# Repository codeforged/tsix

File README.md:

# TSIX

**TSIX** is an **operating system simulator** built entirely in TypeScript on top of Node.js/V8 — complete with a custom kernel, syscall dispatcher, logical Unix-style permission layer (UID/GID, rwx), POSIX-like filesystem, signal handling, and device abstraction (HAL). It is **not a VM that emulates a CPU**; it simulates OS concepts — tasks/processes, permissions, filesystems, signals — directly within the Node.js runtime as an educational and experimental project, and follows **Unix fidelity** as its design north star (see [Philosophy](#philosophy)).

Its flagship use case is a complete **IoT stack** — the MQTNL protocol (MQTT-based), OTA firmware updates, real-time dashboards, and encrypted remote terminal access — all reachable with nothing more than an internet connection and a free MQTT broker. No VPS, no static public IP, no paid cloud service required.

**Where IoT fits (and where it doesn't):** the IoT stack is **not** part of the kernel. TSIX's core — kernel, VFS, drivers (rings 1–2) — is generic within the simulator's ecosystem: it has no idea what MQTT, OTA, or ESP32 are. The IoT stack is simply **one application running on top of the platform**, exactly like the window manager, the file browser, or the shell. That separation *is* the design's strength: one neutral, Unix-faithful core powers any generic simulated task — be it IoT, a desktop environment, or a command line.

TSIX keeps evolving, so expect rough edges and breaking changes between versions.

<p align="center">
  
  <br>
  <em>Ring 1 — Kernel Core (Syscalls, Scheduler, Permission, Mount, GUI Registry).</em>
</p>

<p align="center">
  
  <br>
  <em>Ring 2 — HAL &amp; File System (BKFS, RamFS, HostVFS, device drivers).</em>
</p>

<p align="center">
  
  <br>
  <em>Ring 3 — User Libraries (UserLib, NetworkLib, Emerald, WorkerEntry).</em>
</p>

<p align="center">
  
  <br>
  <em>Ring 4 — Applications (init, shell, daemons, Asteracea WM, GUI apps).</em>
</p>

<p align="center">
  
  <br>
  <em>GUI / Display Pipeline (Emerald → kernel → DOME → browser).</em>
</p>

<p align="center">
  
  <br>
  <em>Networking &amp; IoT Stack (MQTNL → E2E → MQTT → OTA/SCP/TSSH/ESP32).</em>
</p>

<p align="center">
  
  <br>
  <em>TSIX console — TTY login &amp; shell.</em>
</p>

<p align="center">
  
  <br>
  <em>Asteracea Window Manager — desktop environment (taskbar, launcher, apps).</em>
</p>

### Why TSIX exists

This project started in 2021 as a way to remotely manage home automation — lights controlled/monitored by a Raspberry Pi, MCP23017, and relays — while living between two cities and only being home on weekends. Renting a VPS with a static public IP just to check on the lights wasn't worth it. What began as a small utility (originally called **NOS**) grew, over several years, into TSIX: a full operating-system-style platform with an IoT stack as its most complete, most battle-tested application.

---

## Key Features

### Kernel

| Feature                | Detail                                                                                                     |
| ---------------------- | ---------------------------------------------------------------------------------------------------------- |
| **Syscall Dispatcher** | 60+ POSIX-inspired syscalls (OPEN, READ, WRITE, EXEC, WAITPID, SIGNAL, CHMOD...)                           |
| **Scheduler**          | Process manager: PCB states, wait queue, signals (SIGKILL, SIGTERM, SIGINT, SIGSTOP...) — each process runs in its own Worker Thread |
| **Permission Manager** | UID/GID, rwx bits, root bypass, SetUID & Saved UID (suid) support                                          |
| **Mount Manager**      | Multi-VFS overlay, bind mount, union mount, nested mount points                                            |
| **Process Tree**       | Parent-child links, orphan auto-reparent to init, zombie prevention                                        |
| **IPC**                | Built-in `SEND_MSG` syscall + UUID-based identity messaging                                                |

### Filesystem (VFS)

| Feature               | Detail                                                                          |
| --------------------- | ------------------------------------------------------------------------------- |
| **BKFS (SQLite VFS)** | Persistent filesystem in a single `.db` file, path traversal via parent_id tree |
| **RAM VFS**           | In-memory tree for the root filesystem (tmpfs-like)                             |
| **HostVFS**           | Bridge to the host filesystem (`/mnt/host`) via Node.js `fs`                    |
| **Chunked I/O**       | `readChunk`/`writeChunk` for progress-aware file operations                     |
| **Unix Permissions**  | Owner/group/others, mode rwx, SetUID bit                                        |

### Networking

| Feature            | Detail                                                                   |
| ------------------ | ------------------------------------------------------------------------ |
| **MQTNL Protocol** | Binary + JSON encoding, CRC32 validation, magic bytes, version handshake |
| **E2E Encryption** | RSA-2048 handshake + ChaCha20-Poly1305 session encryption                |
| **OTA Updates**    | Over-the-air firmware update via MQTNL protocol                          |
| **SCP**            | Secure file transfer with encryption + password authentication           |
| **TSSH**           | Encrypted remote terminal to a TSIX node from anywhere — internet + MQTT broker only, **no public IP / VPS required**. SSH-like RSA-2048 handshake → ChaCha20-Poly1305 session (successor of AirTerm) |

### Remote Terminal — TSSH (no VPS, no public IP)

**TSSH** is TSIX's encrypted remote terminal (secure shell). Unlike classic SSH, it
**does not need a VPS, a static public IP, or port-forwarding** — it rides on top of
the MQTT broker, which TSIX already speaks natively. The broker can be **local
(LAN)** or **public (internet)** — as long as both sides can reach it, they can
connect.

```
┌─────────────┐        MQTT broker         ┌─────────────┐
│  tssh (client) │  ───── local / internet ───▶  │  tsshd (daemon)  │
│  any TSIX node │                            │  target TSIX node │
└─────────────┘                            └─────────────┘
      │                                          │
      └──  no public IP · no VPS · no NAT hole ◀──┘
```

**Handshake** (SSH-like): the client asks the server's public key, then wraps a
fresh **ChaCha20-Poly1305** session key in **RSA-2048** and sends it back — after
which all terminal I/O is end-to-end encrypted over the MQTT broker.

```mermaid
sequenceDiagram
    autonumber
    participant C as tssh (client)
    participant B as MQTT broker (local/internet)
    participant S as tsshd (daemon)

    C->>B: HANDSHAKE_REQ
    B->>S: HANDSHAKE_REQ
    S-->>B: HANDSHAKE_RESP (RSA-2048 pubkey + fingerprint)
    B-->>C: HANDSHAKE_RESP

    Note over C,S: Verify host fingerprint (known_hosts)

    C->>B: KEY_EXCHANGE (session key, RSA-encrypted)
    B->>S: KEY_EXCHANGE
    S-->>B: CONNECT_ACK
    B-->>C: CONNECT_ACK

    Note over C,S: Session now ChaCha20-Poly1305 encrypted

    C->>B: CONNECT_REQ (encrypted: TTY / -c command)
    B->>S: CONNECT_REQ
    S-->>B: DATA / RESIZE / PING / EXIT (encrypted)
    B-->>C: DATA / RESIZE / PING / EXIT (encrypted)
    C->>B: DATA (keystrokes, encrypted)
    B->>S: DATA
```

**Try it** (two TSIX nodes on the same broker):

```bash
# on the target node
tsshd                # default: listens on MQTNL port 24

# from any other node (or the same one, via localhost)
tssh <hostname>      # e.g. tssh wintsix

tssh <hostname> -c "cat /etc/hostname"   # run a one-off remote command
```

> **Why this matters:** you can administer a TSIX node — or an ESP32 IoT device
> behind NAT — from anywhere, using only a free public MQTT broker. No VPS to
> rent, no firewall hole to open.

### GUI (Emerald + DOME)

| Feature             | Detail                                                                   |
| ------------------- | ------------------------------------------------------------------------ |
| **DOME Engine**     | WebSocket-based display server — renders UI in the browser               |
| **Emerald Widgets** | Screen, Window, button, div, input, lineChart, radialGauge, toggleSwitch |
| **Modal Dialogs**   | alert(), confirm(), question() — built-in                                |
| **Window Manager**  | Asteracea WM with taskbar, Z-index, focus management                     |

### Security

- **Process Isolation** — Each application runs in a separate Worker Thread
- **Sandbox** — Node.js host APIs are restricted in User-Land
- **Permission Model** — Unix rwx for files & devices
- **Root Privileges** — UID 0 bypasses all checks
- **Saved UID** — the login manager (WM) can re-elevate to root to switch users (restore `setuid(0)` via `pcb.suid`)
- **PID 1 Protection** — init cannot be killed directly

---

## Quick Start

### Prerequisites

- Node.js 18+
- npm

### Fresh Install

A fresh TSIX image is built with the `install` script. It creates a brand new database (`.db`) from the bundled root filesystem (`src/mirror` + `src/common`), asks for a few configuration values interactively, and writes them into `src/sysconfig.conf` (key-value, gaya `/etc/fstab.conf`).

```bash
git clone https://github.com/yourusername/tsix.git
cd tsix
npm install
npm run install
```

The installer will ask you for:

- Hostname (interface addresses are derived from it: `<hostname>`, `<hostname>_2`)
- Default login user
- MQTT broker address
- Default MQTT port
- Kernel verbose mode (y/n)
- New database path
- (Optional) root password

> [!NOTE] **Default credentials**
>
> - **User:** `root` — **Password:** `root` (default; bcrypt hash bundled in `src/mirror/etc/shadow`).
> - Change the password by answering the **root-password prompt** during `npm run install`, or run `passwd` inside TSIX.
> - This is a **documented development default**, not a secret. For production or public exposure, always set your own password (don't use the default).

After installation, `src/sysconfig.conf` points to the new database and the system is ready to boot:

```bash
npm start
```

### Install Options

```bash
npm run install                              # interactive, db path from sysconfig
npm run install -- --path data/tsix.db       # install to a specific database file
npm run install -- --path data/tsix.db --force   # overwrite an existing db (auto-backup)
npm run install -- --defaults                # non-interactive, use all defaults
npm run install -- --no-config               # skip writing src/sysconfig.conf
```

### Safe Mode

If the system fails to boot (e.g. a bad daemon in `rc.local`), start it with
the startup scripts disabled:

```bash
npm start -- --safe-mode
```

Safe mode skips `/etc/rc.local` (startup daemons) so you can log in and fix
the problem.

### Utility Scripts

```bash
npm run vfs:bootstrap        # bulk-sync src/mirror into the configured database
npm run bkfs:create          # create an empty database (path from sysconfig)
node scripts/clean_bloat.js  # truncate syslog + vacuum the database
```

All scripts resolve the default database path from `kernel.database` in `src/sysconfig.conf` (shared via `scripts/lib/db-path.ts`), so they stay in sync with the path chosen at install time.

### GUI Mode

```bash
# Terminal 1 — Start DOME Engine
dome

# Open browser -> http://localhost:8080

# Terminal 2 (via TSIX shell) — Launch apps
asteracea           # Window Manager
file-cruiser        # File Manager GUI
eucalyptus          # Text Editor
```

---

## Architecture

```
Ring 0  -> Host OS / V8 Engine (reserved)
Ring 1  -> Kernel Core (Syscalls, Scheduler, Permission Manager)
Ring 2  -> Drivers & File System (HAL, BKFS, Device Drivers)
Ring 3  -> User Libraries (UserLib, FsLib, NetLib, StdLib)
Ring 4  -> Applications (/bin — shell, file-cruiser, tools)
```

> **IoT is not part of the kernel.** The IoT stack runs as a regular
> application in **Ring 4**, on top of the generic rings 1–3 — the kernel has
> no concept of MQTT, OTA, or ESP32. That neutrality is the point: one core
> runs IoT, a desktop environment, and a shell side by side.

### Data Flow

```
Application (Worker Thread)
    | postMessage (IPC)
    v
Syscall Dispatcher (Main Thread)
    | routing
    v
BKFS / Device Drivers / Scheduler
    | return
    v
Syscall Dispatcher
    | postMessage (IPC)
    v
Application
```

### Boot Sequence

```
bootstrap.sh -> main.ts -> Kernel.boot()
  -> Mount BKFS (SQLite VFS) root filesystem
  -> Process /etc/fstab.conf (mount /tmp as ramfs, etc.)
  -> Init TTYs (virtual consoles)
  -> Register Devices (keyboard, TTY, null, network)
  -> Init Serial Auto-Detection
  -> Load Device Configs + HAL drivers
  -> Pre-compile framework libraries into memory cache
  -> Ensure default auth & groups (/etc/passwd, /etc/shadow, users, sudo)
  -> Spawn PID 1 (/bin/init)
  -> init spawns login on TTYs + system daemons
  -> System Ready
```

---

## Project Structure

```
tsix/
├── src/
│   ├── common/        — Shared types (SyscallCode, GUITypes, IPCTypes)
│   ├── kernel/        — Kernel Core (Ring 1)
│   │   ├── Syscalls.ts        — 60+ syscall dispatcher
│   │   ├── Scheduler.ts       — Process manager (create, kill, waitpid)
│   │   ├── PermissionManager.ts — Unix rwx permission check
│   │   ├── MountManager.ts    — Multi-VFS overlay
│   │   ├── PortManager.ts     — TCP/UDP port allocation
│   │   ├── GUIRegistry.ts     — Window -> PID mapping
│   │   └── devices/           — Hardware drivers (TTY, Keyboard, Pipe, Socket...)
│   ├── vfs/           — Filesystem backends (BKFS, RamFS, HostVFS)
│   ├── mirror/        — Userland (Ring 4) — FHS layout (synced to VFS root)
│   │   ├── bin/       — 80+ command-line tools (ls, cat, tsh, sudo...)
│   │   ├── sbin/      — Daemons (tpkgd, scpd, tsshd, crond...)
│   │   ├── usr/       — User binaries (local/bin)
│   │   ├── opt/       — GUI apps (asteracea WM, dome, eucalyptus, file-cruiser...)
│   │   ├── lib/       — Libraries (Emerald, UserLib, Application)
│   │   ├── etc/       — Config (passwd, shadow, group, profile, fstab)
│   │   └── home/, root/, mnt/, var/ — User homes, mounts, logs
│   └── userland/      — Worker entry point
├── wiki/              — Full documentation
├── scripts/           — Build, install & utility scripts
└── platformio/        — ESP32 firmware examples
```

---

## Status

> Note: TSIX is an educational/experimental project. "Working" only means the component passes its test suite and boots in the reference environment — it is **not** production-ready. APIs and behavior may change without notice.

| Component                                                | Status      | Tests       |
| -------------------------------------------------------- | ----------- | ----------- |
| Kernel (syscalls, scheduler, perms, mount, devices, TTY) | Working     | 354/359     |
| VFS (BKFS, HostVFS)                                      | Working     | 150/150     |
| Common Utilities & Protocols (MQTNL)                     | Working     | 140/143     |
| GUI library (Emerald)                                    | Working     | 1/1         |
| **TOTAL**                                                | **Working** | **645/653** |

> [!NOTE] **7 test failures are pre-existing / environment-related** — 5 in `Syscalls` (e.g. `SCREEN_INFO` requires device setup), 2 in `Logger` (timestamp format). Two test files (`SecurityAgent`, `F1-UtilityScripts`) fail to load. Not related to feature changes.

---

## Use Cases

| Area              | Capability                                                         |
| :---------------- | :----------------------------------------------------------------- |
| **IoT Gateway**   | MQTNL protocol, OTA updates, ESP32 integration, Serial devices     |
| **Cloud Desktop** | DOME display server, Asteracea WM, PixelTerm, File Cruiser         |
| **Edge Platform** | TPKG package manager, crond scheduler, process isolation           |
| **Secure Tunnel** | TSSH (remote terminal), SCP (file transfer) with E2E encryption |
| **Dashboard**     | IoT dashboard with real-time charts via DOME                       |
| **Sandbox**       | Isolated script execution in Worker Threads                        |

---

## Philosophy

TSIX is inspired by the **UNIX philosophy**:

1. **Everything is a File** — Keyboard, display, socket, pipe, I2C device — everything is a file
2. **Distributed by Design** — Built-in IPC via SEND_MSG + identity-based messaging
3. **Small, Sharp Tools** — 80+ utilities that combine via pipes & redirection
4. **Security via Simplicity** — UID/GID permission model, process isolation, root privileges
5. **Unix Fidelity** — Emulating Unix/Linux behavior as closely as possible (semantics over mechanism); deviations are permitted only when constrained by the V8 runtime, and must be explicitly documented (see [Five Core Principles](wiki/course/01-philosophy-big-picture.en.md))

---

## Documentation

Official, structured documentation lives in [`wiki/course/`](wiki/course/README.md):

| Page                                             | Description                                        |
| :----------------------------------------------- | :------------------------------------------------- |
| [Course — Overview](wiki/course/README.md)       | Recommended entry point: module index & navigation |
| [Course — Table of Contents](wiki/course/toc.md) | Detailed roadmap with code references              |
| [Course — Format](wiki/course/format.md)         | Documentation style & conventions                  |

The loose files under [`wiki/`](wiki/) are internal working notes (author + AI) and are not part of the official documentation.

---

## Authors

| Name                                             | Role                               |
| :----------------------------------------------- | :--------------------------------- |
| **Andriansah** (andriansah [at] yahoo [dot] com) | Lead Architect & Platform Composer |

---

## Acknowledgments

The TSIX DOME browser client (GUI) builds on these open-source libraries:

| Library                                                               | Version | Purpose                        |  License   |
| --------------------------------------------------------------------- | :-----: | ------------------------------ | :--------: |
| [xterm.js](https://xtermjs.org/)                                      |  5.3.0  | Terminal emulator (PixelTerm)  |    MIT     |
| [CodeMirror](https://codemirror.net/)                                 | 5.65.16 | Text editor (Eucalyptus)       |    MIT     |
| [Fabric.js](http://fabricjs.com/)                                     |  5.3.1  | Canvas rendering (DDC widgets) |    MIT     |
| [Lightweight Charts](https://www.tradingview.com/lightweight-charts/) |  5.2.0  | Real-time charts (dashboard)   | Apache-2.0 |
| [Tabulator](https://www.tabulator.info/) |  6.3.0  |            Data Grid           |    MIT     |

---

## License

MIT License — see the `LICENSE` file for details.

---

<p align="center">
  <i>"Everything is a File, and everyone has their place."</i>
</p>

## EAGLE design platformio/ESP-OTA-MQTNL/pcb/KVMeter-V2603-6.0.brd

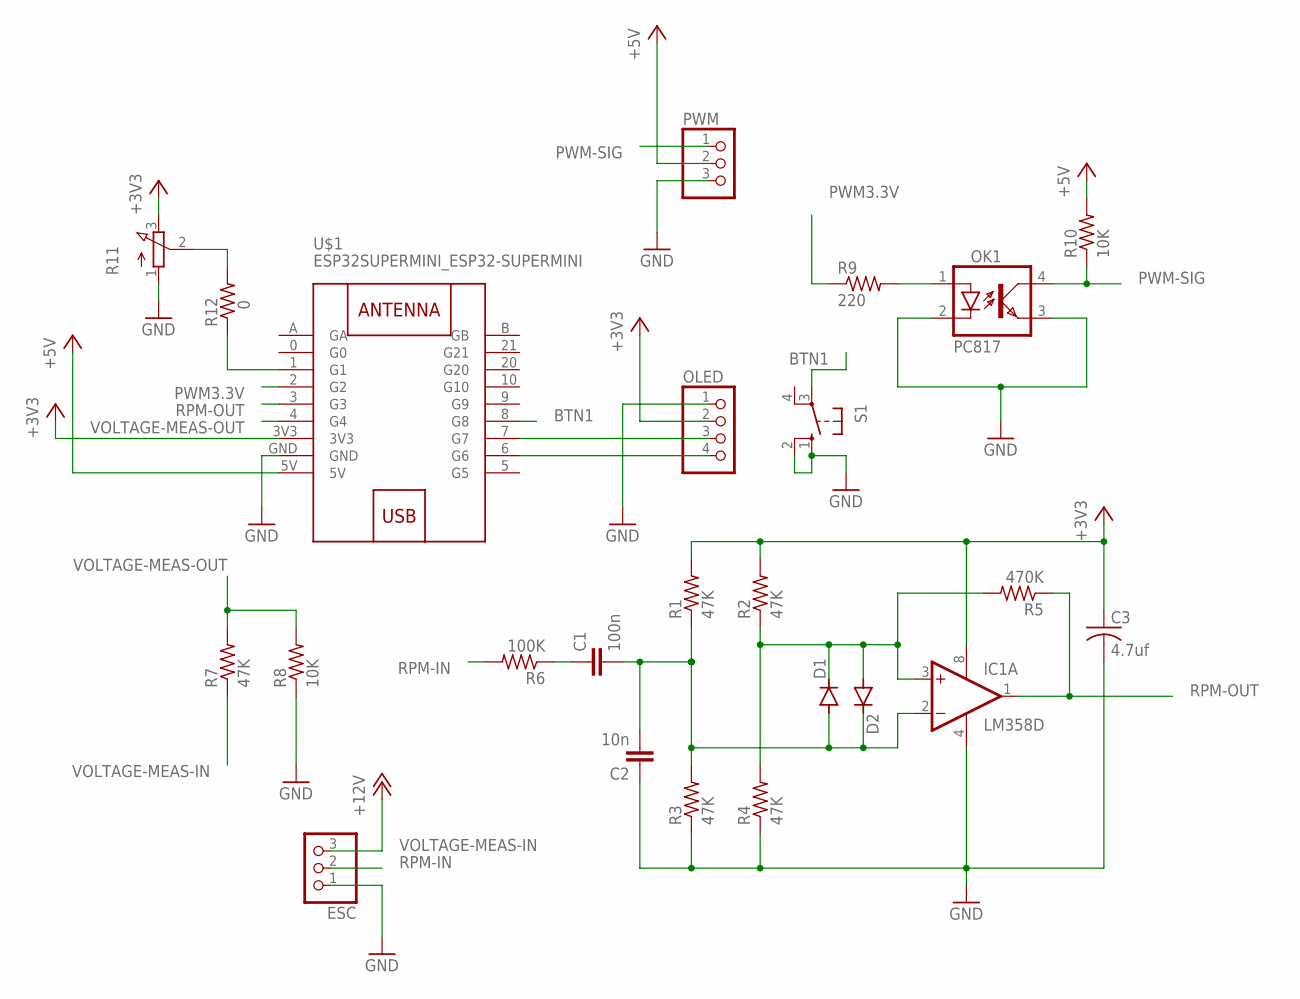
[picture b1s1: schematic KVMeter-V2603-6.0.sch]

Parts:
C1: 100n; C1206
C2: 10n; C1206
C3: 4.7uf; C1206
D1, D2: DIODE-SOD123; SOD123
ESC: PINHD-1X3; 1X03
IC1: LM358D; SO08
OK1: PC817; DIL04
OLED: PINHD-1X4; 1X04
PWM: PINHD-1X3; 1X03
R1, R2, R3, R4, R7: 47K; R1206
R5: 470K; R1206
R6: 100K; R1206
R8, R10: 10K; R1206
R9: 220; R1206
R11: 3RP/1610N
R12: 0; R1206
S1: 10-XX; B3F-10XX
U$1: ESP32SUPERMINI_ESP32-SUPERMINI

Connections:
+3V3: C3.1, IC1.8 (V+), OLED.2, R1.2, R2.2, R11.3 (E), U$1.3V3
+5V: PWM.2, R10.2, U$1.5V
BTN1: S1.3, U$1.8 (G8)
GND: C2.1, C3.2, ESC.1, IC1.4 (V-), OK1.2 (C), OK1.3 (EMIT), OLED.1, PWM.3, R3.1, R4.1, R8.1, R11.1 (A), S1.1 (S), S1.2 (S1), U$1.GND
unnamed: D1.C, D2.A, IC1.3 (+IN), R2.1, R4.2, R5.2
unnamed: R11.2 (S), R12.2
unnamed: C1.1, R6.1
unnamed: R12.1, U$1.1 (G1)
unnamed: OLED.4, U$1.6 (G6)
unnamed: C1.2, C2.2, D1.A, D2.C, IC1.2 (-IN), R1.1, R3.2
unnamed: OLED.3, U$1.7 (G7)
unnamed: OK1.1 (A), R9.2
PWM3.3V: R9.1, U$1.2 (G2)
PWM-SIG: OK1.4 (COL), PWM.1, R10.1
RPM-IN: ESC.2, R6.2
RPM-OUT: IC1.1 (OUT), R5.1, U$1.3 (G3)
VOLTAGE-MEAS-IN: ESC.3, R7.1
VOLTAGE-MEAS-OUT: R7.2, R8.2, U$1.4 (G4)

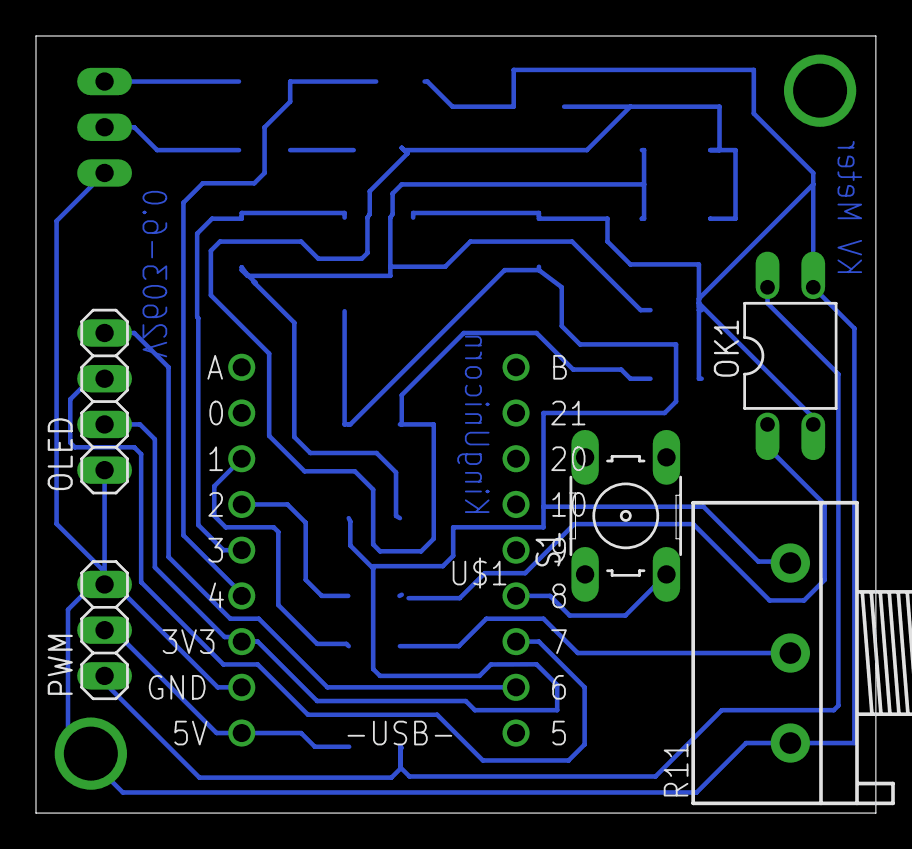
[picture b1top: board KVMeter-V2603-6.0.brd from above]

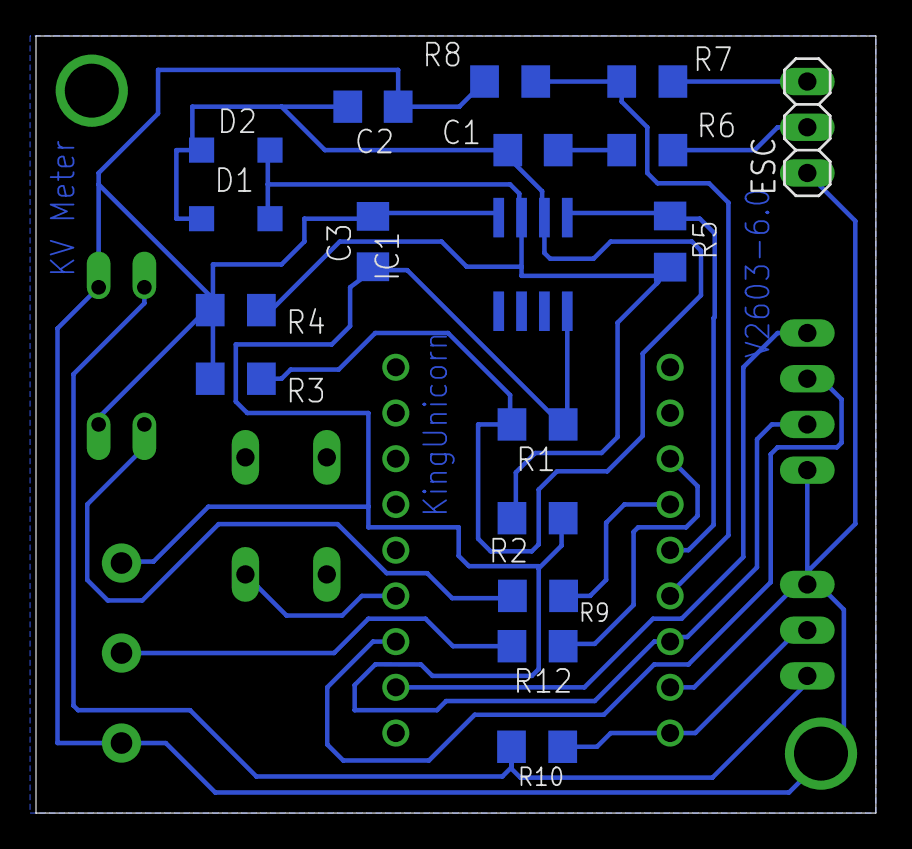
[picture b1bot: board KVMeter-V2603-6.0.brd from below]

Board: 2 copper layers, 46.7 x 43.2 mm, 24 parts (18 on the bottom side), 18 nets.
